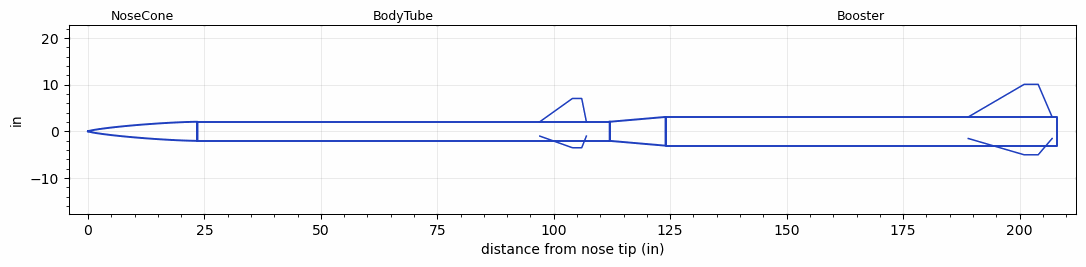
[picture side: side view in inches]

<RASAeroDocument>
 <FileVersion>2</FileVersion>
 <RocketDesign>
  <NoseCone>
   <Length>23.5</Length>
   <Diameter>4.1</Diameter>
   <Shape>Von Karman Ogive</Shape>
   <Location>0</Location>
  </NoseCone>
  <BodyTube>
   <Length>88.5</Length>
   <Diameter>4.1</Diameter>
   <Location>23.5</Location>
   <Fin>
    <Count>3</Count>
    <Chord>10</Chord>
    <Span>5</Span>
    <SweepDistance>7</SweepDistance>
    <TipChord>2</TipChord>
    <Thickness>0.125</Thickness>
    <Location>15</Location>
    <AirfoilSection>Hexagonal</AirfoilSection>
    <FX1>0.5</FX1>
    <FX3>0.5</FX3>
   </Fin>
  </BodyTube>
  <Booster>
   <Length>84</Length>
   <Diameter>6.17</Diameter>
   <InsideDiameter>4.1</InsideDiameter>
   <Location>112</Location>
   <ShoulderLength>12</ShoulderLength>
   <Fin>
    <Count>3</Count>
    <Chord>18</Chord>
    <Span>7</Span>
    <SweepDistance>12</SweepDistance>
    <TipChord>3</TipChord>
    <Thickness>0.125</Thickness>
    <Location>19</Location>
    <AirfoilSection>Hexagonal</AirfoilSection>
    <FX1>1</FX1>
    <FX3>1</FX3>
   </Fin>
  </Booster>
  <Surface>Smooth Paint</Surface>
  <ModifiedBarrowman>True</ModifiedBarrowman>
  <Turbulence>True</Turbulence>
  <UseBooster1>False</UseBooster1>
  <UseBooster2>False</UseBooster2>
 </RocketDesign>
 <LaunchSite>
  <Altitude>3000</Altitude>
  <Pressure>0</Pressure>
  <RodAngle>0</RodAngle>
  <RodLength>40</RodLength>
  <Temperature>74</Temperature>
  <WindSpeed>0</WindSpeed>
 </LaunchSite>
 <Recovery>
  <Altitude1>1000</Altitude1>
  <Altitude2>1000</Altitude2>
  <DeviceType1>None</DeviceType1>
  <DeviceType2>None</DeviceType2>
  <Event1>False</Event1>
  <Event2>False</Event2>
  <Size1>1</Size1>
  <Size2>1</Size2>
  <EventType1>None</EventType1>
  <EventType2>None</EventType2>
  <CD1>1.33</CD1>
  <CD2>1.33</CD2>
 </Recovery>
 <SimulationList>
  <Simulation>
   <SustainerEngine>O3400-IM-P  (CTI)</SustainerEngine>
   <SustainerLaunchWt>57.5</SustainerLaunchWt>
   <SustainerNozzleDiameter>2.7</SustainerNozzleDiameter>
   <SustainerCG>73</SustainerCG>
   <SustainerIgnitionDelay>10</SustainerIgnitionDelay>
   <Booster1Engine>P8000  (CTI)</Booster1Engine>
   <Booster1LaunchWt>216</Booster1LaunchWt>
   <Booster1SeparationDelay>0.5</Booster1SeparationDelay>
   <Booster1IgnitionDelay>0</Booster1IgnitionDelay>
   <Booster1CG>143.4</Booster1CG>
   <Booster1NozzleDiameter>6</Booster1NozzleDiameter>
   <IncludeBooster1>True</IncludeBooster1>
   <Booster2Delay>0</Booster2Delay>
   <IncludeBooster2>False</IncludeBooster2>
   <TimetoApogee>133.5586</TimetoApogee>
   <MaxAltitude>233158.1</MaxAltitude>
   <MaxVelocity>4090.206</MaxVelocity>
  </Simulation>
  <Simulation>
   <SustainerEngine>O3400-IM-XX  (CTI)</SustainerEngine>
   <SustainerLaunchWt>49.5</SustainerLaunchWt>
   <SustainerNozzleDiameter>3.9</SustainerNozzleDiameter>
   <SustainerCG>73</SustainerCG>
   <SustainerIgnitionDelay>10</SustainerIgnitionDelay>
   <Booster1Engine>P-7700-XX  (CTI)</Booster1Engine>
   <Booster1LaunchWt>178</Booster1LaunchWt>
   <Booster1SeparationDelay>0.5</Booster1SeparationDelay>
   <Booster1IgnitionDelay>0</Booster1IgnitionDelay>
   <Booster1CG>143</Booster1CG>
   <Booster1NozzleDiameter>5.8</Booster1NozzleDiameter>
   <IncludeBooster1>True</IncludeBooster1>
   <Booster2Delay>0</Booster2Delay>
   <IncludeBooster2>False</IncludeBooster2>
   <TimetoApogee>264.9899</TimetoApogee>
   <MaxAltitude>946742.7</MaxAltitude>
   <MaxVelocity>7404.33</MaxVelocity>
  </Simulation>
 </SimulationList>
</RASAeroDocument>
